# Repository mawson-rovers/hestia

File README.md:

# Hestia

Hestia is a cubesat circuit board developed by Mawson Rovers in support of
[UTS Resilient Space Computing initiative][uts]. It is designed to provide
temperature control and monitoring for a demonstration heatsink payload which
will be launched aboard the [Waratah Seed satellite][ws] on a SpaceX rocket
in early 2024.

[ws]: https://www.waratahseed.space
[uts]: https://web-tools.uts.edu.au/projects/detail.cfm?ProjectId=PRO22-15177

Hestia was the Greek goddess of home and hearth, and similar to that, our Hestia
board provides a home and warmth to the UTS heatsink.

## Project structure

This project has four primary modules:

* **hestia-pcb** - the circuit board design for the cubesat, as a KiCAD 7 project
* **hestia-fw** - the firmware for the MSP430 microcontroller on the Hestia board,
    responsible for controlling the heater and measuring temperature, written in C
* **hestia-sat** - the payload control software to be run on a BeagleBone Black
    on board the Waratah Seed satellite, written in Rust
* **hestia-dash** - a web dashboard for monitoring and operating the board, used
    primarily for testing and written in Python

All the software projects require customised build environments, and more details
can be found in their respective READMEs.

The project also has a **scripts/** folder which is used for automated builds on
GitHub, and **ws-1/** folder for interface information from our host Waratah Seed
satellite.

## Project team

The project is led by [Dr Nick Bennett][nick], Senior Lecturer at UTS, with
software and electronics development managed by [Matt Ryall][matt] from Mawson
Rovers. [John Dowdell][jd] and [Scott Fraser][scott] developed the Hestia
components for the mission.

[nick]: https://profiles.uts.edu.au/Nicholas.Bennett
[matt]: https://github.com/mryall-mawson
[scott]: https://github.com/Scouttman
[jd]: https://github.com/JDMawson

The project was funded by [SmartSat CRC](https://smartsatcrc.com), a
federally-funded Collaborative Research Centre, and the [University of
Technology, Sydney (UTS)](https://www.uts.edu.au).

## Licensing

Mawson Rovers has made the cubesat payload designs, firmware and software available under [an MIT License](LICENSE).

Please feel free to learn from this code and reuse it on future space missions under the terms of the license. However, we will not be taking external contributions to this code.

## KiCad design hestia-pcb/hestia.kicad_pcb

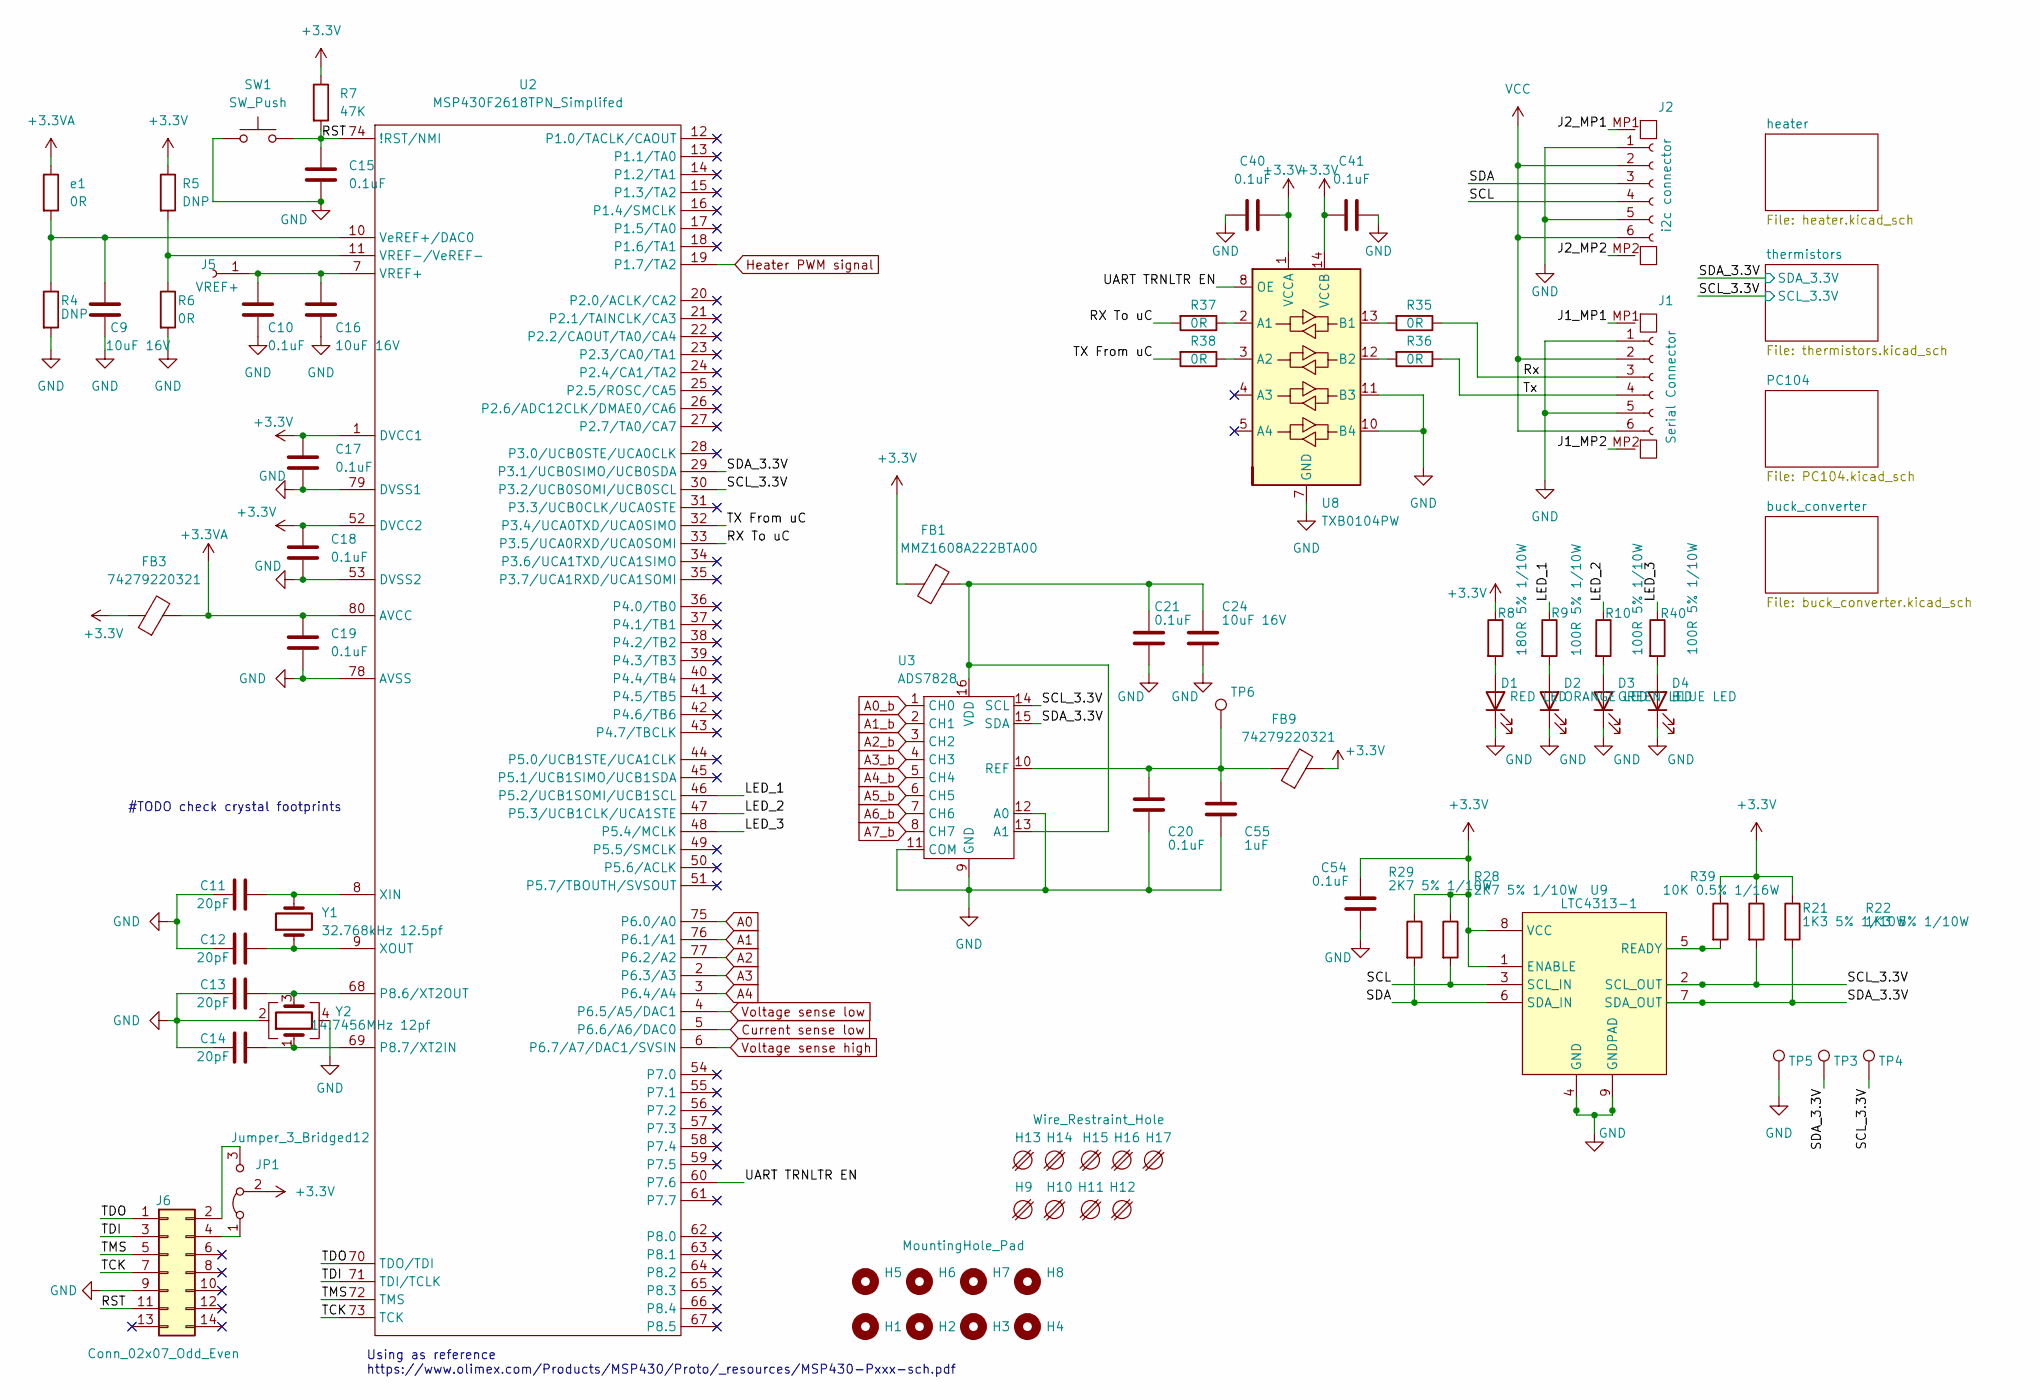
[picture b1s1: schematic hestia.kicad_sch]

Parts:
C9, C16, C24: 10uF 16V; C_0603_1608Metric_Pad1.08x0.95mm_HandSolder; Mfr PN CC0603MRX5R7BB106; Digikey Part 311-1822-1-ND
C10, C15, C17, C18, C19, C20, C21, C40, C41, C54: 0.1uF; C_0603_1608Metric_Pad1.08x0.95mm_HandSolder; Mfr PN CL10B104KB8WPND; Digikey Part 1276-CL10B104KB8WPNDCT-ND
C11, C12, C13, C14: 20pF; C_0603_1608Metric_Pad1.08x0.95mm_HandSolder; Mfr PN C0603C200G4HAC7867; Digikey Part 399-C0603C200G4HAC7867CT-ND
C55: 1uF; C_0603_1608Metric_Pad1.08x0.95mm_HandSolder; Mfr PN 0603ZC105MAT2A; Digikey Part 478-12231-1-ND
D1: RED LED; LED_0805_2012Metric_Pad1.15x1.40mm_HandSolder; Mfr PN LS R976-NR-1; Digikey Part 475-1278-1-ND
D2: ORANGE LED; LED_0805_2012Metric_Pad1.15x1.40mm_HandSolder; Mfr PN LO R976-PS-1; Digikey Part 475-2488-1-ND
D3: GREEN LED; LED_0805_2012Metric_Pad1.15x1.40mm_HandSolder; Mfr PN LG R971-KN-1; Digikey Part 475-1410-1-ND
D4: BLUE LED; LED_0805_2012Metric_Pad1.15x1.40mm_HandSolder; Mfr PN 150080BS75000; Digikey Part 732-4982-1-ND
FB1: MMZ1608A222BTA00; R_0603_1608Metric_Pad0.98x0.95mm_HandSolder; Mouser Part 810-MMZ1608A222BTA00
FB3, FB9: 74279220321; R_0805_2012Metric_Pad1.20x1.40mm_HandSolder; Mfr PN 74279220321; Digikey Part 732-6125-1-ND
H1, H2, H3, H4: MountingHole; MountingHole_3.2mm_M3_ISO7380
H5, H6, H7, H8: MountingHole_Pad; PC104_Pad_Hole_3P18_6P35
H9, H10, H11, H12, H13, H14, H15: Wire_Restraint_Hole; Wire_Restraint_Hole_1.8mm
H16, H17: Wire_Restraint_Hole; Wire_Restraint_Hole_1.9mm
J1: Serial Connector; MolexPicoLock_6Way_2MP; Mfr PN 5040500691; Digikey Part WM10143CT-ND
J2: i2c connector; MolexPicoLock_6Way_2MP; Mfr PN 5040500691; Digikey Part WM10143CT-ND
J5: VREF+; TestPoint_Pad_D2.0mm
J6: Conn_02x07_Odd_Even; IDC-Header_2x07_P2.54mm_Vertical; Mfr PN SBH11-PBPC-D07-ST-BK; Digikey Part S9170-ND
JP1: Jumper_3_Bridged12; PinHeader_1x03_P1.27mm_Vertical; Mfr PN M50-3530342; Digikey Part 952-3599-ND
R4, R5: DNP; R_0603_1608Metric_Pad0.98x0.95mm_HandSolder
R6, R35, R36, R37, R38: 0R; R_0603_1608Metric_Pad0.98x0.95mm_HandSolder; Mfr PN RMCF0603ZT0R00; Digikey Part RMCF0603ZT0R00CT-ND
R7: 47K; R_0603_1608Metric_Pad0.98x0.95mm_HandSolder; Mfr PN ERJ-PA3J473V; Digikey Part P47KBZCT-ND
R8: 180R 5% 1/10W; R_0603_1608Metric_Pad0.98x0.95mm_HandSolder; Mfr PN RC0603JR-13100RL; Digikey Part 311-180GRCT-ND
R9, R10, R40: 100R 5% 1/10W; R_0603_1608Metric_Pad0.98x0.95mm_HandSolder; Mfr PN RC0603JR-13100RL; Digikey Part 13-RC0603JR-13100RLCT-ND
R21, R22: 1K3 5% 1/10W; R_0603_1608Metric_Pad0.98x0.95mm_HandSolder; Mfr PN RC0603JR-071K3L; Digikey Part 311-1.3KGRCT-ND
R28, R29: 2K7 5% 1/10W; R_0603_1608Metric_Pad0.98x0.95mm_HandSolder; Mfr PN RC0603JR-072K7L; Digikey Part 311-2.7KGRCT-ND
R39: 10K 0.5% 1/16W; R_0603_1608Metric_Pad0.98x0.95mm_HandSolder; Mfr PN RR0816P-103-D; Digikey Part RR08P10.0KDCT-ND
SW1: SW_Push; SW_SPST_PTS810; Mfr PN PTS810 SJK 250 SMTR LFS; Digikey Part CKN10503CT-ND
TP3, TP4, TP5, TP6: TestPoint; TestPoint_Pad_2.0x2.0mm
U2: MSP430F2618TPN_Simplifed; LQFP-80_12x12mm_P0.5mm; Mfr PN MSP430F2618TPN; Digikey Part 296-26224-ND
U3: ADS7828; TSSOP-16_4.4x5mm_P0.65mm; Mfr PN ADS7828E/2K5; Digikey Part 296-38856-1-ND
U8: TXB0104PW; TSSOP-14_4.4x5mm_P0.65mm; Mfr PN TXB0104QPWRQ1; Digikey Part 296-27760-1-ND
U9: LTC4313-1; DFN-8-1EP_3x3mm_P0.5mm_EP1.65x2.38mm; Mfr PN LTC4313IDD-1#PBF; Digikey Part 505-LTC4313IDD-1#PBF-ND
Y1: 32.768kHz 12.5pf; CM7V-T1A; Mfr PN CM7VT1A32.768KHZ125PF20PPMTBQAT3; Digikey Part 2195-CM7VT1A32.768KHZ125PF20PPMTBQAT3CT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
Y2: 14.7456MHz 12pf; ecx-32_crystal; Mfr PN ECS-147.4-12-33-AGN-TR; Digikey Part XC2437CT-ND
e1: 0R; R_0603_1608Metric_Pad0.98x0.95mm_HandSolder; Mfr PN RMCF0603ZT0R00; Digikey Part RMCF0603ZT0R00CT-ND

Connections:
+3.3V: C17.2, C18.1, C40.1, C41.1, C54.1, FB1.2, FB3.1, FB9.2, JP1.2 (C), R5.1, R7.1, R8.1, R21.1, R22.1, R28.1, R29.1, R39.1, U2.1 (DVCC1), U2.52 (DVCC2), U8.1 (VCCA), U8.14 (VCCB), U9.1 (ENABLE), U9.8 (VCC); also elsewhere on the board
+3.3VA: C19.1, FB3.2, U2.80 (AVCC), e1.1
/J1_MP1: J1.MP1
/J1_MP2: J1.MP2
/J2_MP1: J2.MP1
/J2_MP2: J2.MP2
/LED_1: R9.1, U2.46 (P5.2/UCB1SOMI/UCB1SCL)
/LED_2: R10.1, U2.47 (P5.3/UCB1CLK/UCA1STE)
/LED_3: R40.1, U2.48 (P5.4/MCLK)
/RST: C15.1, J6.11, R7.2, SW1.2, U2.74 (!RST/NMI)
/RX To uC: R37.2, U2.33 (P3.5/UCA0RXD/UCA0SOMI)
/Rx: J1.3, R35.1
/SCL: J2.4, R28.2, U9.3 (SCL_IN)
/SCL_3.3V: R21.2, TP4.1, U2.30 (P3.2/UCB0SOMI/UCB0SCL), U3.14 (SCL), U9.2 (SCL_OUT); also elsewhere on the board
/SDA: J2.3, R29.2, U9.6 (SDA_IN)
/SDA_3.3V: R22.2, TP3.1, U2.29 (P3.1/UCB0SIMO/UCB0SDA), U3.15 (SDA), U9.7 (SDA_OUT); also elsewhere on the board
/TCK: J6.7, U2.73 (TCK)
/TDI: J6.3, U2.71 (TDI/TCLK)
/TDO: J6.1, U2.70 (TDO/TDI)
/TMS: J6.5, U2.72 (TMS)
/TX From uC: R38.2, U2.32 (P3.4/UCA0TXD/UCA0SIMO)
/Tx: J1.4, R36.1
/UART TRNLTR EN: U2.60 (P7.6), U8.8 (OE)
A0: U2.75 (P6.0/A0); also elsewhere on the board
A0_b: U3.1 (CH0); also elsewhere on the board
A1: U2.76 (P6.1/A1); also elsewhere on the board
A1_b: U3.2 (CH1); also elsewhere on the board
A2: U2.77 (P6.2/A2); also elsewhere on the board
A2_b: U3.3 (CH2); also elsewhere on the board
A3: U2.2 (P6.3/A3); also elsewhere on the board
A3_b: U3.4 (CH3); also elsewhere on the board
A4: U2.3 (P6.4/A4); also elsewhere on the board
A4_b: U3.5 (CH4); also elsewhere on the board
A5_b: U3.6 (CH5); also elsewhere on the board
A6_b: U3.7 (CH6); also elsewhere on the board
A7_b: U3.8 (CH7); also elsewhere on the board
Current sense low: U2.5 (P6.6/A6/DAC0); also elsewhere on the board
Heater PWM signal: U2.19 (P1.7/TA2); also elsewhere on the board
unnamed: D1.2 (A), R8.2
unnamed: D2.2 (A), R9.2
unnamed: D3.2 (A), R10.2
unnamed: D4.2 (A), R40.2
unnamed: C10.1, C16.1, J5.1, U2.7 (VREF+)
unnamed: J6.2, JP1.3 (B)
unnamed: J6.4, JP1.1 (A)
unnamed: C13.2, U2.68 (P8.6/XT2OUT), Y2.3
unnamed: C14.2, U2.69 (P8.7/XT2IN), Y2.1
unnamed: C9.1, R4.1, U2.10 (VeREF+/DAC0), e1.2
unnamed: C11.2, U2.8 (XIN), Y1.2
unnamed: C12.2, U2.9 (XOUT), Y1.1
unnamed: C21.1, C24.1, FB1.1, U3.13 (A1), U3.16 (VDD)
unnamed: C20.1, C55.1, FB9.1, TP6.1, U3.10 (REF)
unnamed: R37.1, U8.2 (A1)
unnamed: R38.1, U8.3 (A2)
unnamed: R35.2, U8.13 (B1)
unnamed: R36.2, U8.12 (B2)
unnamed: R39.2, U9.5 (READY)
VCC: J1.2, J1.6, J2.2, J2.6; also elsewhere on the board
Voltage sense high: U2.6 (P6.7/A7/DAC1/SVSIN); also elsewhere on the board
Voltage sense low: U2.4 (P6.5/A5/DAC1); also elsewhere on the board

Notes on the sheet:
#TODO check crystal footprints
Using as reference https://www.olimex.com/Products/MSP430/Proto/_resources/MSP430-Pxxx-sch.pdf

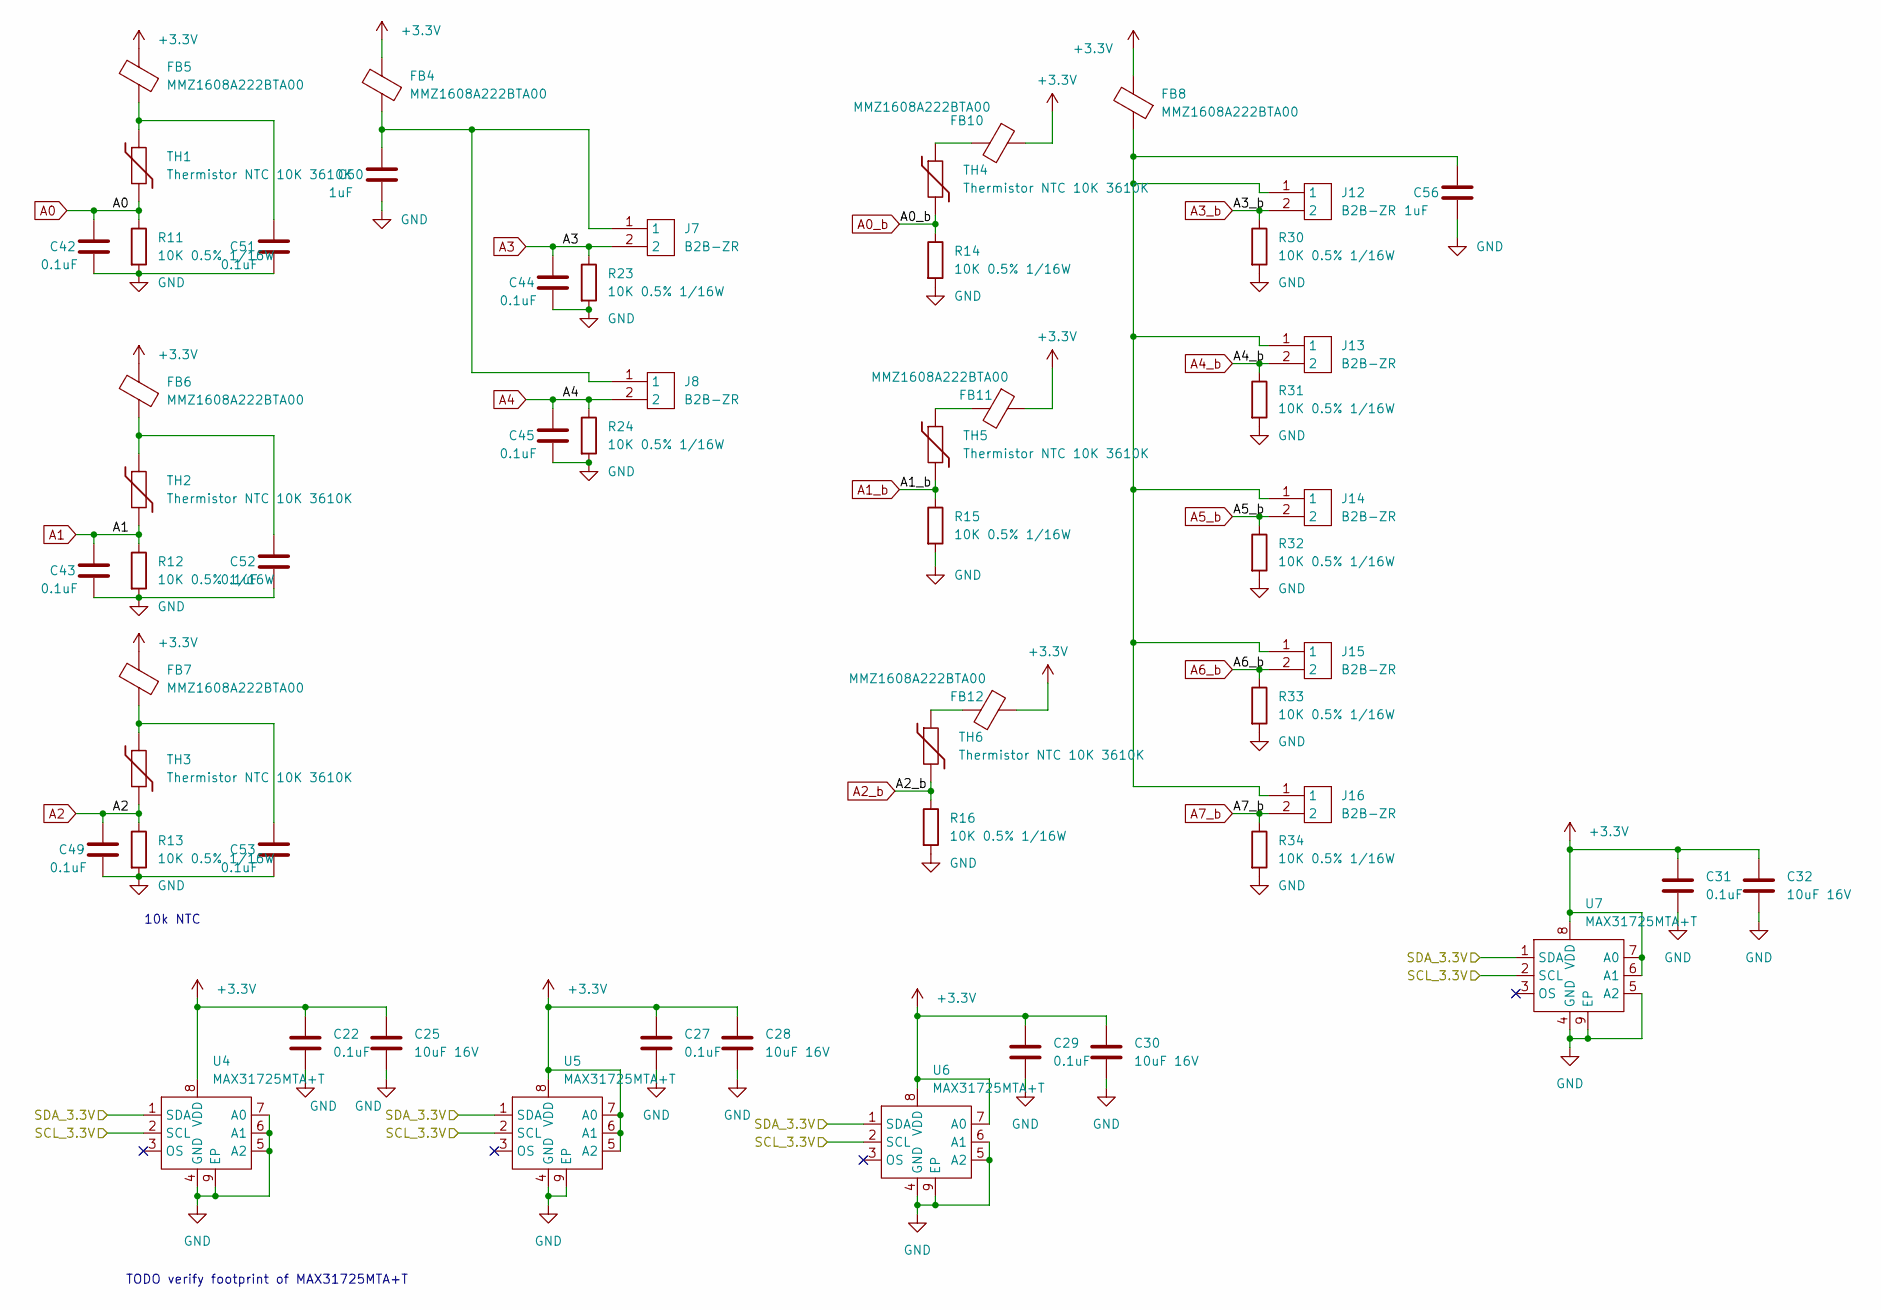
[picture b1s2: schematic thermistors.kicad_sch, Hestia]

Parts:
C22, C27, C29, C31, C42, C43, C44, C45, C49, C51, C52, C53: 0.1uF; C_0603_1608Metric_Pad1.08x0.95mm_HandSolder; Mfr PN CL10B104KB8WPND; Digikey Part 1276-CL10B104KB8WPNDCT-ND
C25, C28, C30, C32: 10uF 16V; C_0603_1608Metric_Pad1.08x0.95mm_HandSolder; Mfr PN CC0603MRX5R7BB106; Digikey Part 311-1822-1-ND
C50, C56: 1uF; C_0603_1608Metric_Pad1.08x0.95mm_HandSolder; Mfr PN 0603ZC105MAT2A; Digikey Part 478-12231-1-ND
FB4, FB5, FB6, FB7, FB8, FB10, FB11, FB12: MMZ1608A222BTA00; R_0603_1608Metric_Pad0.98x0.95mm_HandSolder; Mouser Part 810-MMZ1608A222BTA00
J7, J8, J12, J13, J14, J15, J16: B2B-ZR; B2B-ZR(LF)(SN); Mfr PN B2B-ZR(LF)(SN); Digikey Part 455-1657-ND
R11, R12, R13, R14, R15, R16, R23, R24, R30, R31, R32, R33, R34: 10K 0.5% 1/16W; R_0603_1608Metric_Pad0.98x0.95mm_HandSolder; Mfr PN RR0816P-103-D; Digikey Part RR08P10.0KDCT-ND
TH1, TH2, TH3, TH4, TH5, TH6: Thermistor NTC 10K 3610K; R_0603_1608Metric_Pad0.98x0.95mm_HandSolder; Mfr PN NTCS0603E3103JMT; Digikey Part BC2289CT-ND
U4, U5, U6, U7: MAX31725MTA+T; DFN-8-1EP_3x3mm_P0.65mm_EP1.55x2.4mm; Mfr PN MAX31725MTA+T; Digikey Part MAX31725MTA+TCT-ND

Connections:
+3.3V: C22.1, C25.1, C27.1, C28.1, C29.1, C30.1, C31.1, C32.1, FB4.2, FB5.2, FB6.2, FB7.2, FB8.2, FB10.1, FB11.1, FB12.1, U4.8 (VDD), U5.5 (A2), U5.6 (A1), U5.7 (A0), U5.8 (VDD), U6.7 (A0), U6.8 (VDD), U7.6 (A1), U7.7 (A0), U7.8 (VDD); also elsewhere on the board
/SCL_3.3V: U4.2 (SCL), U5.2 (SCL), U6.2 (SCL), U7.2 (SCL); also elsewhere on the board
/SDA_3.3V: U4.1 (SDA), U5.1 (SDA), U6.1 (SDA), U7.1 (SDA); also elsewhere on the board
A0: C42.1, R11.1, TH1.2; also elsewhere on the board
A0_b: R14.1, TH4.2; also elsewhere on the board
A1: C43.1, R12.1, TH2.2; also elsewhere on the board
A1_b: R15.1, TH5.2; also elsewhere on the board
A2: C49.1, R13.1, TH3.2; also elsewhere on the board
A2_b: R16.1, TH6.2; also elsewhere on the board
A3: C44.1, J7.2, R23.1; also elsewhere on the board
A3_b: J12.2, R30.1; also elsewhere on the board
A4: C45.1, J8.2, R24.1; also elsewhere on the board
A4_b: J13.2, R31.1; also elsewhere on the board
A5_b: J14.2, R32.1; also elsewhere on the board
A6_b: J15.2, R33.1; also elsewhere on the board
A7_b: J16.2, R34.1; also elsewhere on the board
unnamed: C50.1, FB4.1, J7.1, J8.1
unnamed: C51.1, FB5.1, TH1.1
unnamed: C52.1, FB6.1, TH2.1
unnamed: C53.1, FB7.1, TH3.1
unnamed: C56.1, FB8.1, J12.1, J13.1, J14.1, J15.1, J16.1
unnamed: FB10.2, TH4.1
unnamed: FB11.2, TH5.1
unnamed: FB12.2, TH6.1

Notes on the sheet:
TODO verify footprint of MAX31725MTA+T
10k NTC

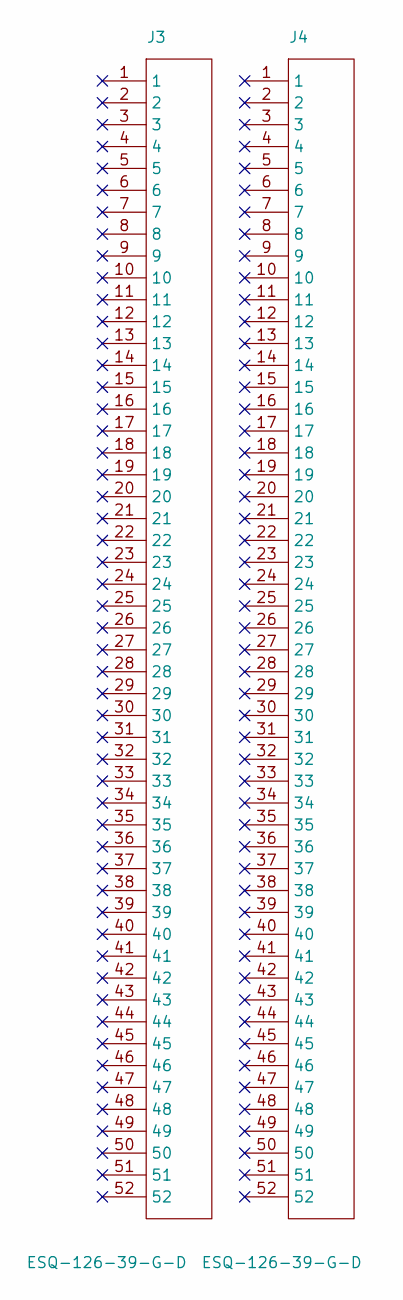
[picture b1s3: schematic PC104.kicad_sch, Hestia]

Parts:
J3, J4: ESQ-126-39-G-D

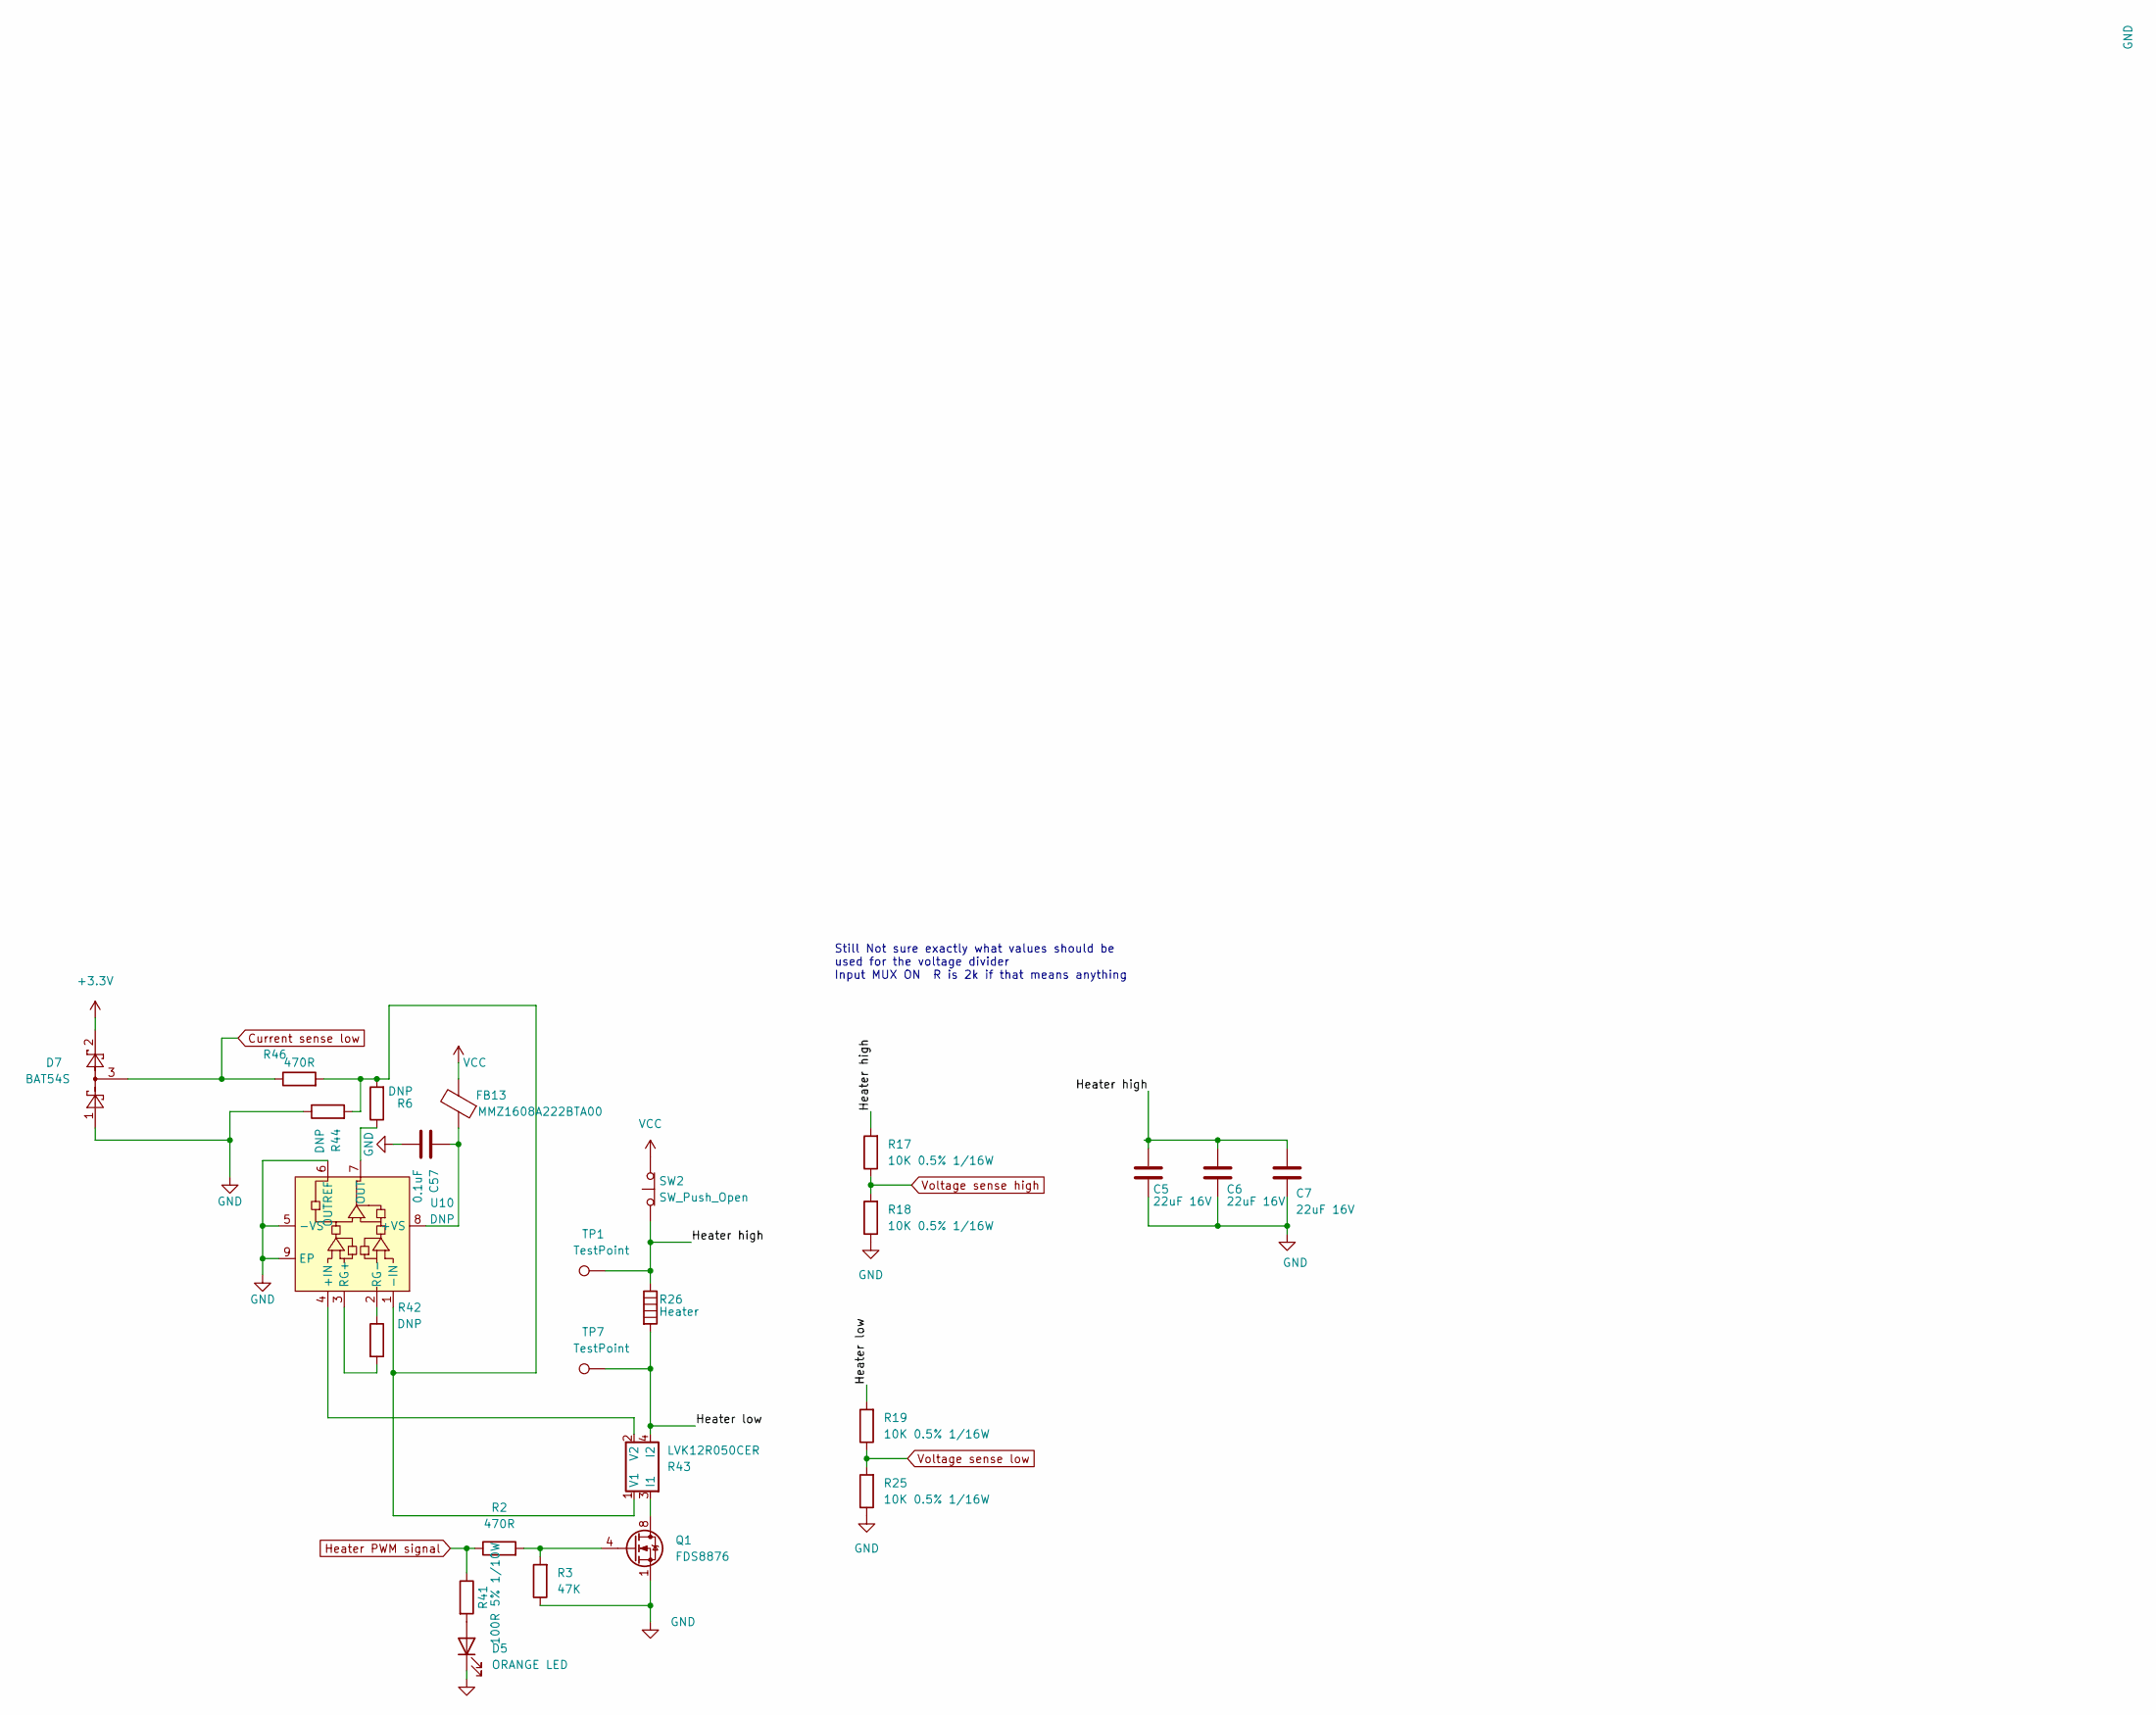
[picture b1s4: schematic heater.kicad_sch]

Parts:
C5, C6, C7: 22uF 16V; C_1206_3216Metric; Mfr PN CL31A226MOCLNNC; LCSC Part C13585
C57: 0.1uF; C_0603_1608Metric_Pad1.08x0.95mm_HandSolder; Mfr PN CL10B104KB8WPND; Digikey Part 1276-CL10B104KB8WPNDCT-ND
D5: ORANGE LED; LED_0805_2012Metric_Pad1.15x1.40mm_HandSolder; Mfr PN LO R976-PS-1; Digikey Part 475-2488-1-ND
D7: BAT54S; SOT-323_SC-70_Handsoldering; Mfr PN BAT54SWT1G; Digikey Part BAT54SWT1GOSCT-ND
FB13: MMZ1608A222BTA00; R_0603_1608Metric_Pad0.98x0.95mm_HandSolder; Mouser Part 810-MMZ1608A222BTA00
Q1: FDS8876; SOIC-8_3.9x4.9mm_P1.27mm; Mouser Part 512-FDS8876
R2, R46: 470R; R_0603_1608Metric_Pad0.98x0.95mm_HandSolder; Mfr PN ESR03EZPF4700; Digikey Part RHM470ADCT-ND
R3: 47K; R_0603_1608Metric_Pad0.98x0.95mm_HandSolder; Mfr PN ERJ-PA3J473V; Digikey Part P47KBZCT-ND
R6: DNP; R_0402_1005Metric_Pad0.72x0.64mm_HandSolder; Mfr PN RMCF0603ZT0R00; Digikey Part RMCF0603ZT0R00CT-ND
R17, R18, R19, R25: 10K 0.5% 1/16W; R_0603_1608Metric_Pad0.98x0.95mm_HandSolder; Mfr PN RR0816P-103-D; Digikey Part RR08P10.0KDCT-ND
R26: Heater; NetTie-2_SMD_Pad0.5mm
R41: 100R 5% 1/10W; R_0603_1608Metric_Pad0.98x0.95mm_HandSolder; Mfr PN RC0603JR-13100RL; Digikey Part 13-RC0603JR-13100RLCT-ND
R42: DNP; C_0402_1005Metric; Mfr PN ERA-2AEB4990X; Digikey Part P499DCCT-ND
R43: LVK12R050CER; LVK12R010CER; Mfr PN LVK12R010CER; Digikey Part 273-LVK12R050CERCT-ND
R44: DNP; R_0603_1608Metric_Pad0.98x0.95mm_HandSolder; Mfr PN RR0816P-103-D; Digikey Part RR08P10.0KDCT-ND
SW2: SW_Push_Open; Thermal Switch
TP1: TestPoint; TestPoint_Pad_2.0x2.0mm
TP7: TestPoint; TestPoint_Pad_1.0x1.0mm
U10: DNP; WSON-8-1EP_3x3mm_P0.5mm_EP1.2x2mm; Mfr PN INA826AIDRGR; Digikey Part 296-36596-1-ND

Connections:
+3.3V: D7.2; also elsewhere on the board
/heater/Heater high: C5.1, C6.1, C7.1, R17.2, R26.1, SW2.1 (A), TP1.1
/heater/Heater low: R19.2, R26.2, R43.4 (I2), TP7.1
Current sense low: D7.3, R46.1; also elsewhere on the board
Heater PWM signal: R2.1, R41.1; also elsewhere on the board
unnamed: D5.2 (A), R41.2
unnamed: Q1.4 (G), R2.2, R3.2
unnamed: Q1.5 (D), Q1.6 (D), Q1.7 (D), Q1.8 (D), R43.3 (I1)
unnamed: R43.2 (V2), U10.4 (+IN)
unnamed: C57.1, FB13.1, U10.8 (+VS)
unnamed: R42.2, U10.3 (RG+)
unnamed: R42.1, U10.2 (RG-)
VCC: FB13.2, SW2.2 (B); also elsewhere on the board
Voltage sense high: R17.1, R18.2; also elsewhere on the board
Voltage sense low: R19.1, R25.2; also elsewhere on the board

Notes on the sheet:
Still Not sure exactly what values should be used for the voltage divider Input MUX ON R is 2k if that means anything

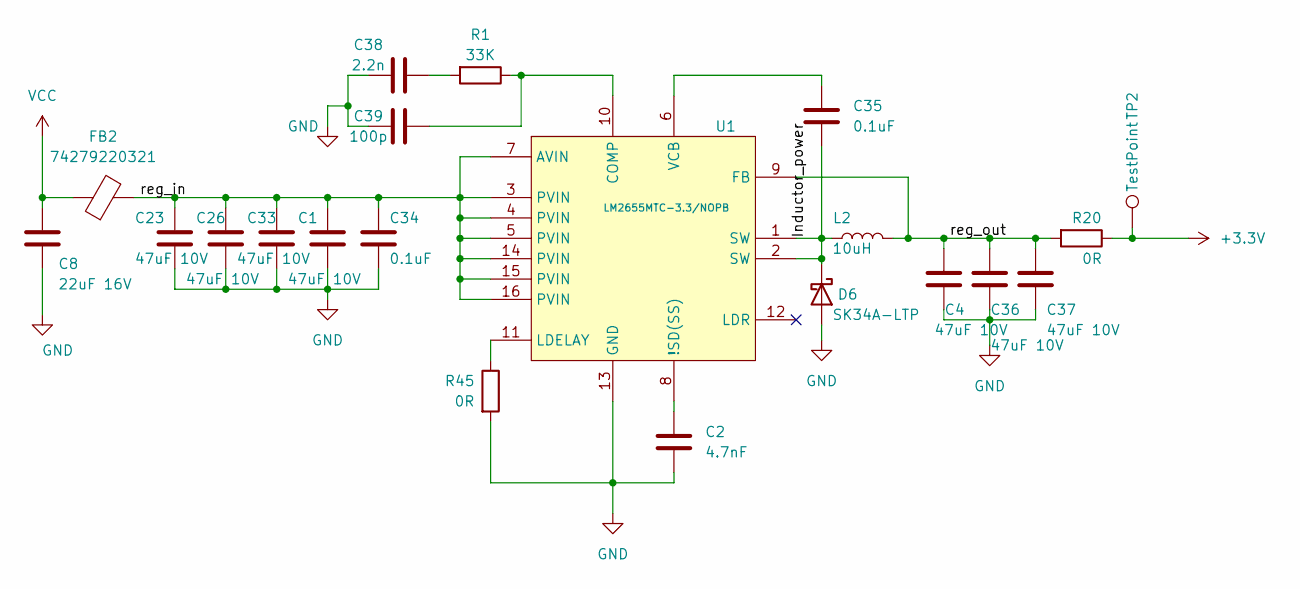
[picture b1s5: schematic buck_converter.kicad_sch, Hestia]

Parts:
C1, C4, C23, C26, C33, C36, C37: 47uF 10V; C_0805_2012Metric_Pad1.18x1.45mm_HandSolder; Mfr PN LMK212BBJ476MG-T; Digikey Part 587-5465-1-ND
C2: 4.7nF; C_0603_1608Metric_Pad1.08x0.95mm_HandSolder; Mfr PN CL10B472KB8WPNC; Digikey Part 1276-6532-1-ND
C8: 22uF 16V; C_1206_3216Metric; Mfr PN CL31A226MOCLNNC; LCSC Part C13585
C34, C35: 0.1uF; C_0603_1608Metric_Pad1.08x0.95mm_HandSolder; Mfr PN CL10B104KB8WPND; Digikey Part 1276-CL10B104KB8WPNDCT-ND
C38: 2.2n; C_0603_1608Metric_Pad1.08x0.95mm_HandSolder; Mfr PN C0603C222K5RACAUTO; Digikey Part 399-6871-1-ND
C39: 100p; C_0603_1608Metric_Pad1.08x0.95mm_HandSolder; Mfr PN VJ0603A101FXACW1BC; Digikey Part 720-1649-1-ND
D6: SK34A-LTP; D_SMA; Mfr PN SK34A-LTP; Digikey Part SK34A-LTPMSCT-ND
FB2: 74279220321; R_0805_2012Metric_Pad1.20x1.40mm_HandSolder; Mfr PN 74279220321; Digikey Part 732-6125-1-ND
L2: 10uH; SRP5030C; Mfr PN SRP5030C-100M; Digikey Part 118-SRP5030C-100MCT-ND
R1: 33K; R_0603_1608Metric_Pad0.98x0.95mm_HandSolder; Mfr PN ERJ-PA3F3302V; Digikey Part P33KBYCT-ND
R20: 0R; R_1210_3225Metric_Pad1.30x2.65mm_HandSolder; Mfr PN RC1210JR-070RL; Digikey Part YAG3375CT-ND
R45: 0R; R_0603_1608Metric_Pad0.98x0.95mm_HandSolder; Mfr PN RMCF0603ZT0R00; Digikey Part RMCF0603ZT0R00CT-ND
TP2: TestPoint; TestPoint_Pad_2.0x2.0mm
U1: LM2655MTC-3.3/NOPB; TSSOP-16_4.4x5mm_P0.65mm; Mfr PN LM2655MTC-3.3/NOPB; Digikey Part LM2655MTC-3.3/NOPB-ND

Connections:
+3.3V: R20.1, TP2.1; also elsewhere on the board
/buck_converter/Inductor_power: C35.2, D6.1 (K), L2.2, U1.1 (SW), U1.2 (SW)
/buck_converter/reg_in: C1.1, C23.1, C26.1, C33.1, C34.2, FB2.2, U1.3 (PVIN), U1.4 (PVIN), U1.5 (PVIN), U1.7 (AVIN), U1.14 (PVIN), U1.15 (PVIN), U1.16 (PVIN)
/buck_converter/reg_out: C4.1, C36.1, C37.1, L2.1, R20.2, U1.9 (FB)
unnamed: C38.1, R1.2
unnamed: C2.1, U1.8 (!SD(SS))
unnamed: C39.1, R1.1, U1.10 (COMP)
unnamed: R45.1, U1.11 (LDELAY)
unnamed: C35.1, U1.6 (VCB)
VCC: C8.1, FB2.1; also elsewhere on the board

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
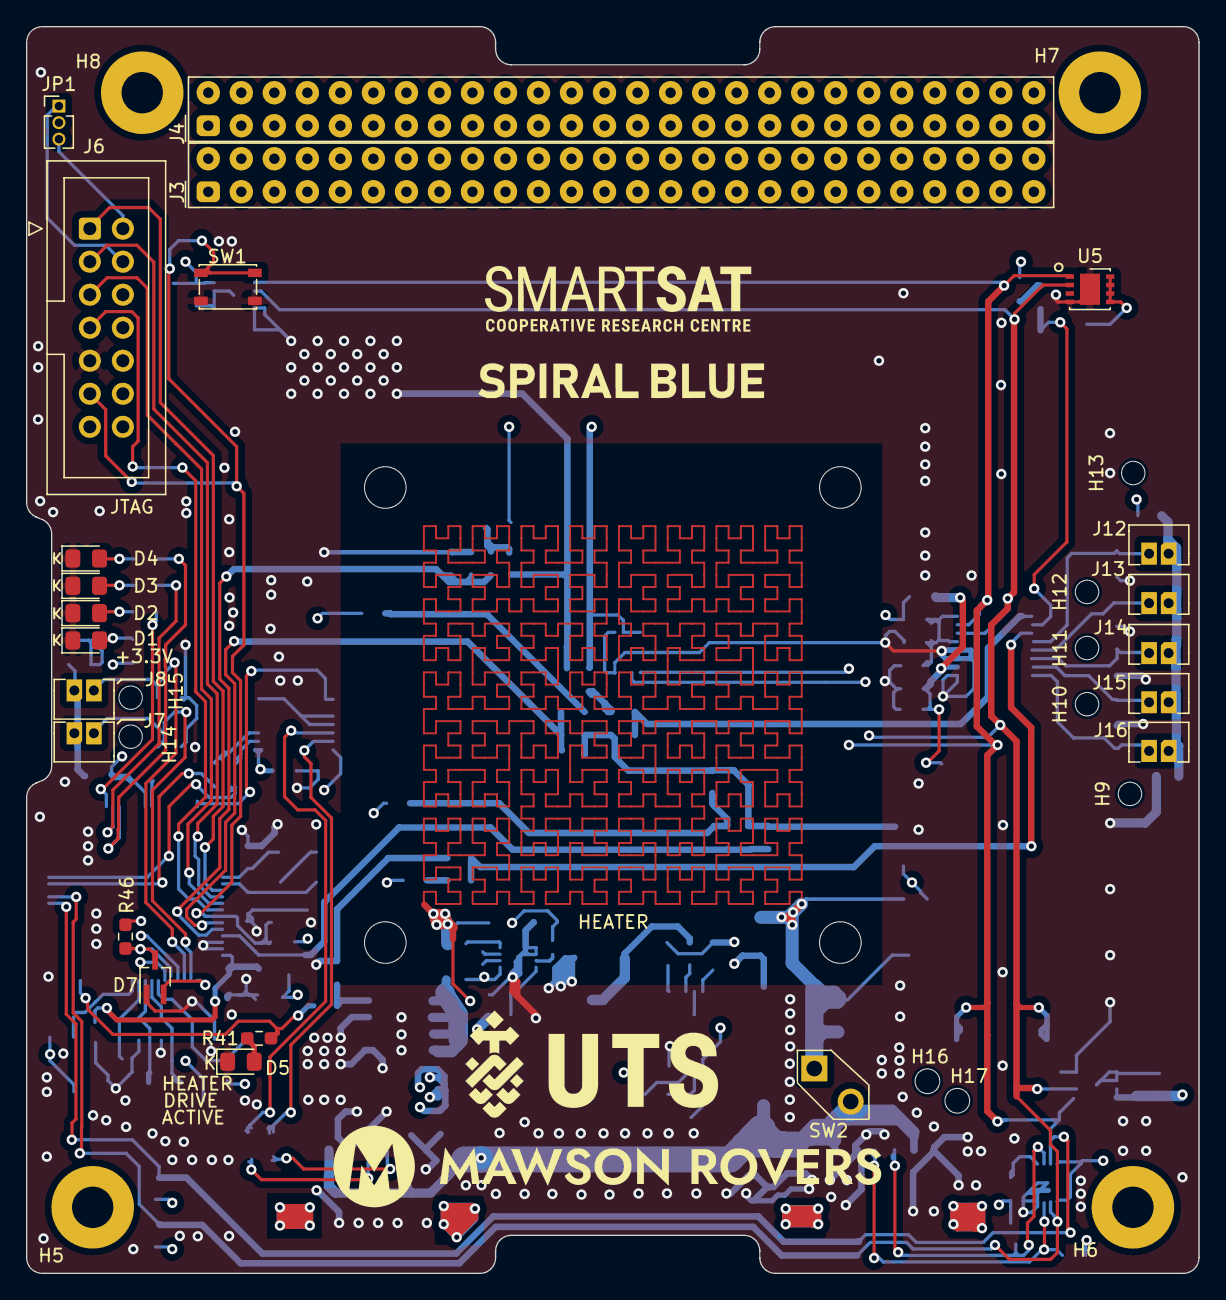
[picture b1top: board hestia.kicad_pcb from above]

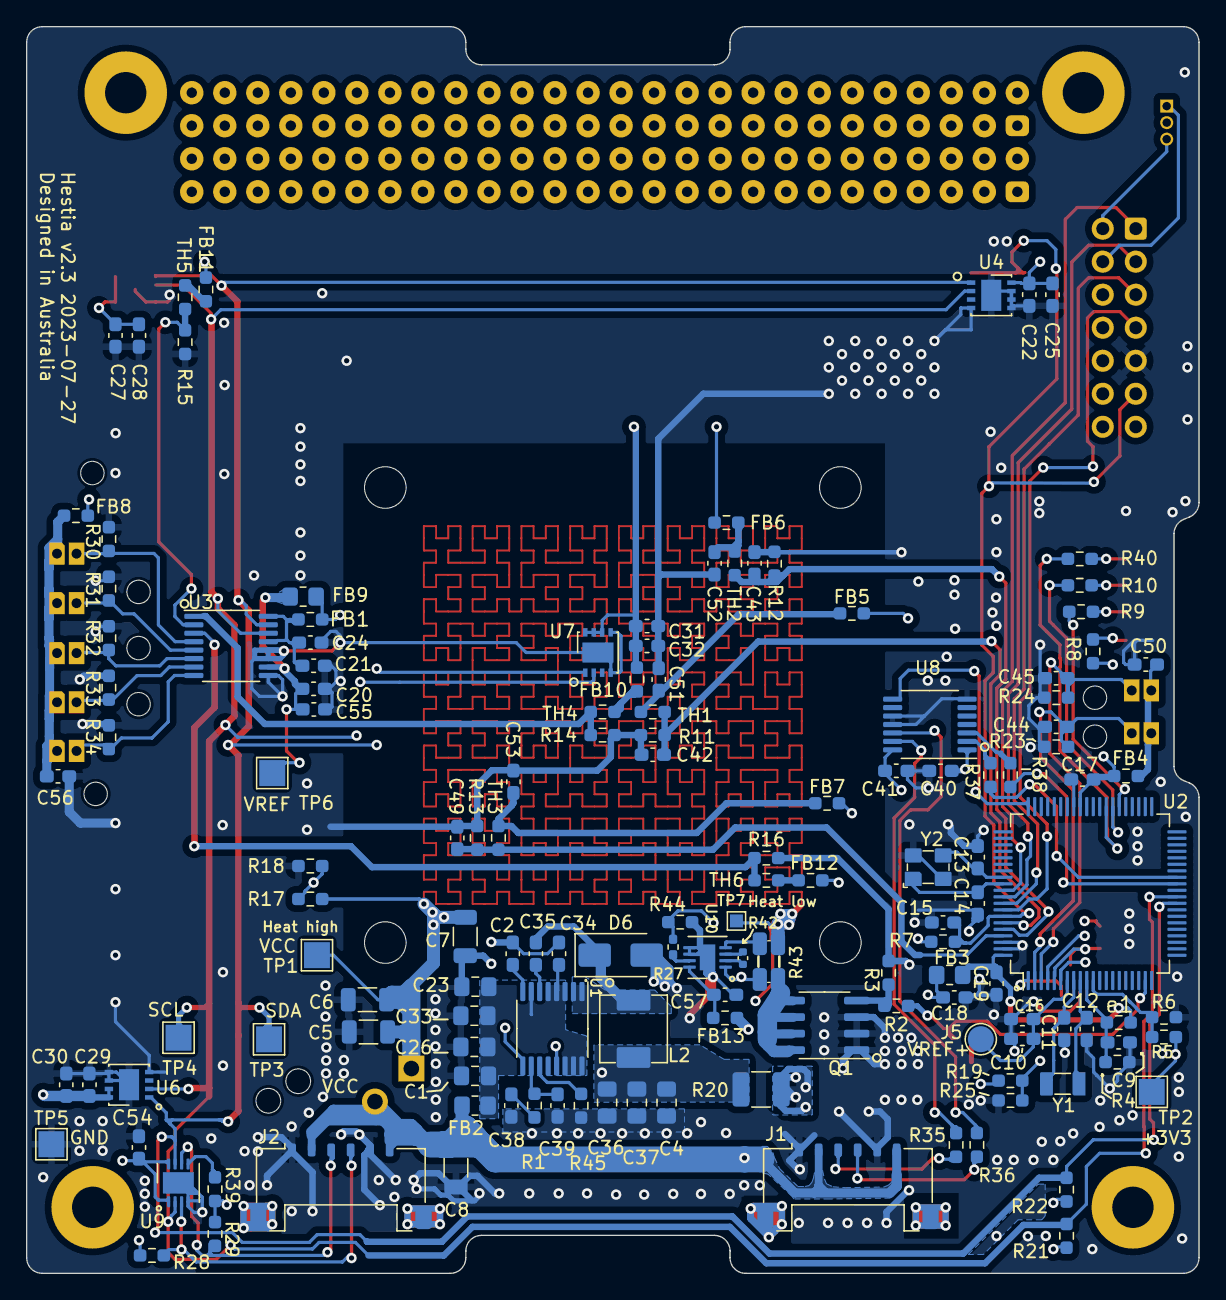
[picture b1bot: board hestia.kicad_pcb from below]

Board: 4 copper layers, 90.2 x 95.9 mm, 184 parts (140 on the bottom side), 85 nets.

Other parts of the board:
LOGO1: MAWSON ROVERS; Logo_Mawson_Rovers_2
LOGO2: UTS; Logo_UTS_2
LOGO3: SMARTSATCRC; Logo_SmartSatCRC
LOGO4: SPIRALBLUE; Logo_SpiralBlue
R27: DNP; R_0402_1005Metric_Pad0.72x0.64mm_HandSolder
